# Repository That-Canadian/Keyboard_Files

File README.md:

My Open Source keyboard files will be places here.

-- TODO: Better README --

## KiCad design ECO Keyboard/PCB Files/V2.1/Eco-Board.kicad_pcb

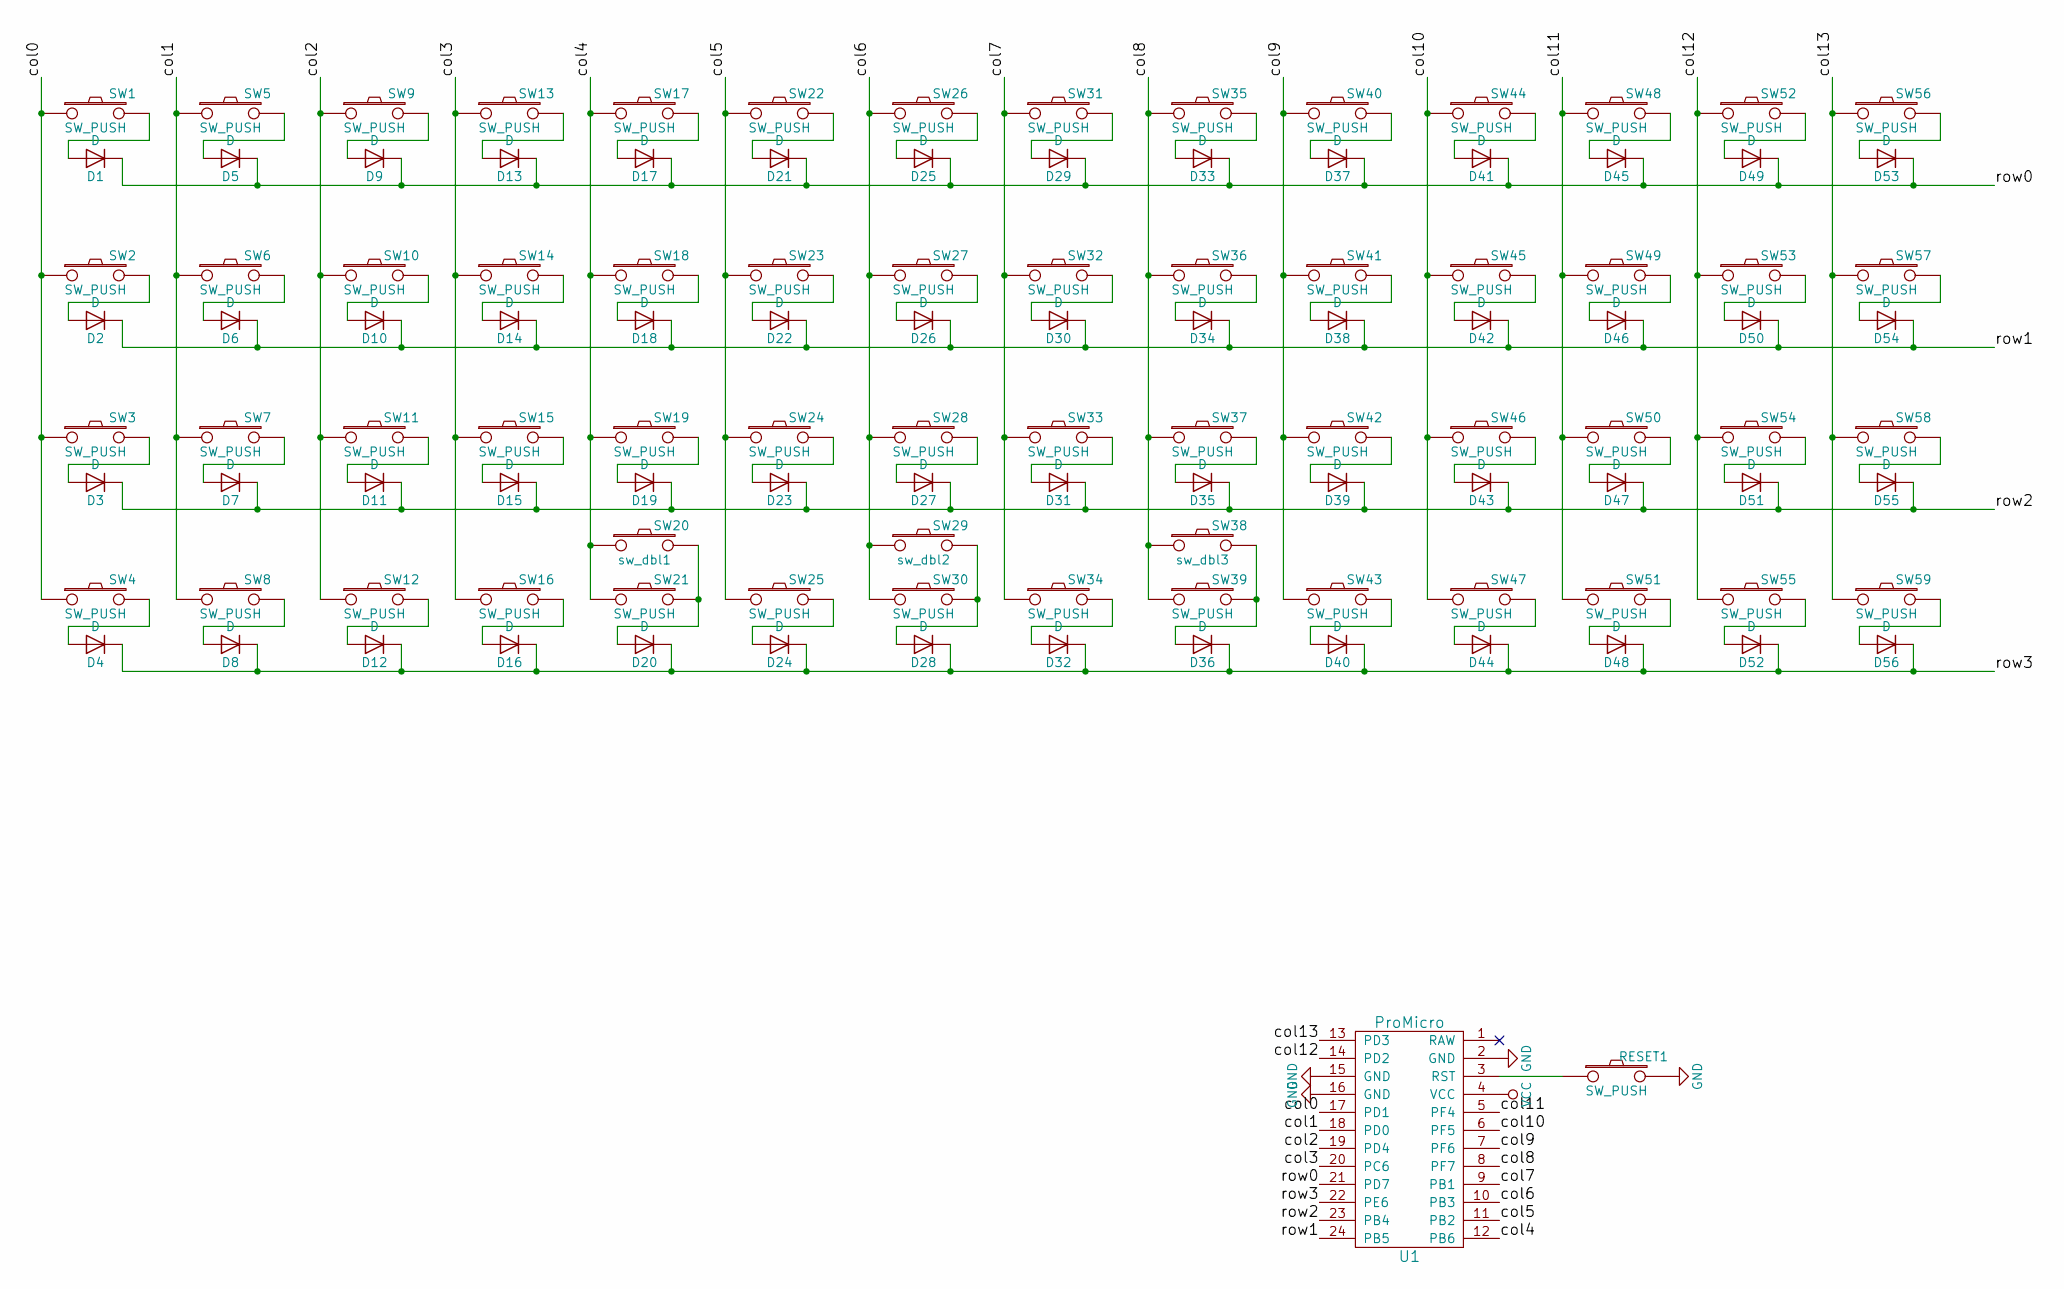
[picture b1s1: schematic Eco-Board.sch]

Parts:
D1, D2, D3, D4, D5, D6, D7, D8, D9, D10, D11, D12, D13, D14, D15, D16, D17, D18, D19, D20, D21, D22, D23, D24, D25, D26, D27, D28, D29, D30, D31, D32, D33, D34, D35, D36, D37, D38, D39, D40, D41, D42, D43, D44, D45, D46, D47, D48, D49, D50, D51, D52, D53, D54, D55, D56: D; D_SOD123_ThroughHole
RESET1: SW_PUSH; SW_TACT_ALPS_SKQGABE010
SW1, SW2, SW3, SW4, SW5, SW6, SW7, SW8, SW9, SW10, SW11, SW12, SW13, SW14, SW15, SW16, SW17, SW18, SW19, SW21, SW22, SW23, SW24, SW25, SW26, SW27, SW28, SW30, SW31, SW32, SW33, SW34, SW35, SW36, SW37, SW39, SW40, SW41, SW42, SW43, SW44, SW45, SW46, SW47, SW48, SW49, SW50, SW51, SW52, SW53, SW54, SW55, SW56, SW57, SW58, SW59: SW_PUSH; Mx_Alps_100
SW20: sw_dbl1; Mx_Alps_200
SW29: sw_dbl2; Mx_Alps_200
SW38: sw_dbl3; Mx_Alps_200
U1: ProMicro; Pro_Micro

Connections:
/col0: SW1.1, SW2.1, SW3.1, SW4.1, U1.17 (PD1)
/col1: SW5.1, SW6.1, SW7.1, SW8.1, U1.18 (PD0)
/col2: SW9.1, SW10.1, SW11.1, SW12.1, U1.19 (PD4)
/col3: SW13.1, SW14.1, SW15.1, SW16.1, U1.20 (PC6)
/col4: SW17.1, SW18.1, SW19.1, SW20.1, SW21.1, U1.12 (PB6)
/col5: SW22.1, SW23.1, SW24.1, SW25.1, U1.11 (PB2)
/col6: SW26.1, SW27.1, SW28.1, SW29.1, SW30.1, U1.10 (PB3)
/col7: SW31.1, SW32.1, SW33.1, SW34.1, U1.9 (PB1)
/col8: SW35.1, SW36.1, SW37.1, SW38.1, SW39.1, U1.8 (PF7)
/col9: SW40.1, SW41.1, SW42.1, SW43.1, U1.7 (PF6)
/col10: SW44.1, SW45.1, SW46.1, SW47.1, U1.6 (PF5)
/col11: SW48.1, SW49.1, SW50.1, SW51.1, U1.5 (PF4)
/col12: SW52.1, SW53.1, SW54.1, SW55.1, U1.14 (PD2)
/col13: SW56.1, SW57.1, SW58.1, SW59.1, U1.13 (PD3)
/row0: D1.1 (K), D5.1 (K), D9.1 (K), D13.1 (K), D17.1 (K), D21.1 (K), D25.1 (K), D29.1 (K), D33.1 (K), D37.1 (K), D41.1 (K), D45.1 (K), D49.1 (K), D53.1 (K), U1.21 (PD7)
/row1: D2.1 (K), D6.1 (K), D10.1 (K), D14.1 (K), D18.1 (K), D22.1 (K), D26.1 (K), D30.1 (K), D34.1 (K), D38.1 (K), D42.1 (K), D46.1 (K), D50.1 (K), D54.1 (K), U1.24 (PB5)
/row2: D3.1 (K), D7.1 (K), D11.1 (K), D15.1 (K), D19.1 (K), D23.1 (K), D27.1 (K), D31.1 (K), D35.1 (K), D39.1 (K), D43.1 (K), D47.1 (K), D51.1 (K), D55.1 (K), U1.23 (PB4)
/row3: D4.1 (K), D8.1 (K), D12.1 (K), D16.1 (K), D20.1 (K), D24.1 (K), D28.1 (K), D32.1 (K), D36.1 (K), D40.1 (K), D44.1 (K), D48.1 (K), D52.1 (K), D56.1 (K), U1.22 (PE6)
GND: RESET1.2, U1.2 (GND), U1.15 (GND), U1.16 (GND)
unnamed: D1.2 (A), SW1.2
unnamed: D2.2 (A), SW2.2
unnamed: D3.2 (A), SW3.2
unnamed: D4.2 (A), SW4.2
unnamed: D5.2 (A), SW5.2
unnamed: D6.2 (A), SW6.2
unnamed: D7.2 (A), SW7.2
unnamed: D8.2 (A), SW8.2
unnamed: D9.2 (A), SW9.2
unnamed: D10.2 (A), SW10.2
unnamed: D11.2 (A), SW11.2
unnamed: D12.2 (A), SW12.2
unnamed: D13.2 (A), SW13.2
unnamed: D14.2 (A), SW14.2
unnamed: D15.2 (A), SW15.2
unnamed: D16.2 (A), SW16.2
unnamed: D17.2 (A), SW17.2
unnamed: D18.2 (A), SW18.2
unnamed: D19.2 (A), SW19.2
unnamed: D20.2 (A), SW20.2, SW21.2
unnamed: D21.2 (A), SW22.2
unnamed: D22.2 (A), SW23.2
unnamed: D23.2 (A), SW24.2
unnamed: D24.2 (A), SW25.2
unnamed: D25.2 (A), SW26.2
unnamed: D26.2 (A), SW27.2
unnamed: D27.2 (A), SW28.2
unnamed: D28.2 (A), SW29.2, SW30.2
unnamed: D29.2 (A), SW31.2
unnamed: D30.2 (A), SW32.2
unnamed: D31.2 (A), SW33.2
unnamed: D32.2 (A), SW34.2
unnamed: D33.2 (A), SW35.2
unnamed: D34.2 (A), SW36.2
unnamed: D35.2 (A), SW37.2
unnamed: D36.2 (A), SW38.2, SW39.2
unnamed: D37.2 (A), SW40.2
unnamed: D38.2 (A), SW41.2
unnamed: D39.2 (A), SW42.2
unnamed: D40.2 (A), SW43.2
unnamed: D41.2 (A), SW44.2
unnamed: D42.2 (A), SW45.2
unnamed: D43.2 (A), SW46.2
unnamed: D44.2 (A), SW47.2
unnamed: D45.2 (A), SW48.2
unnamed: D46.2 (A), SW49.2
unnamed: D47.2 (A), SW50.2
unnamed: D48.2 (A), SW51.2
unnamed: D49.2 (A), SW52.2
unnamed: D50.2 (A), SW53.2
unnamed: D51.2 (A), SW54.2
unnamed: D52.2 (A), SW55.2
unnamed: D53.2 (A), SW56.2
unnamed: D54.2 (A), SW57.2
unnamed: D55.2 (A), SW58.2
unnamed: D56.2 (A), SW59.2
unnamed: RESET1.1, U1.3 (RST)
VCC: U1.4 (VCC)

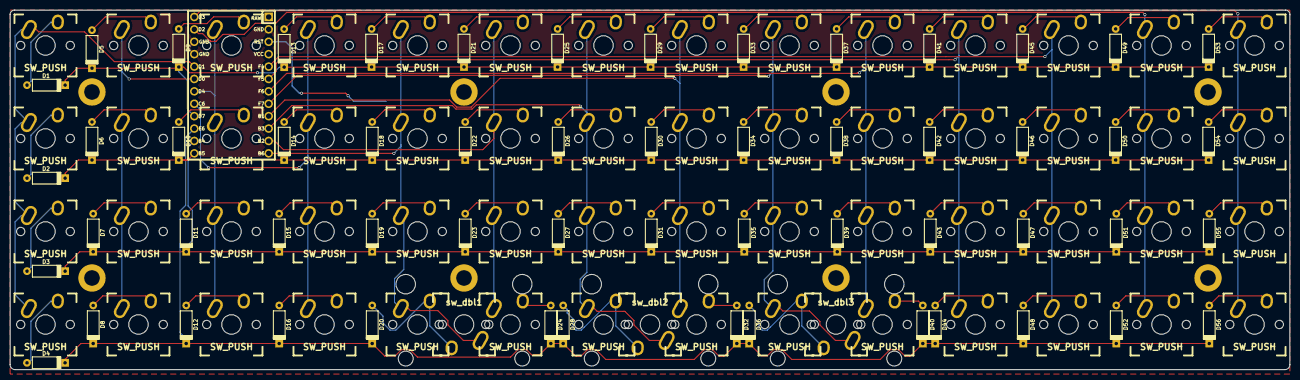
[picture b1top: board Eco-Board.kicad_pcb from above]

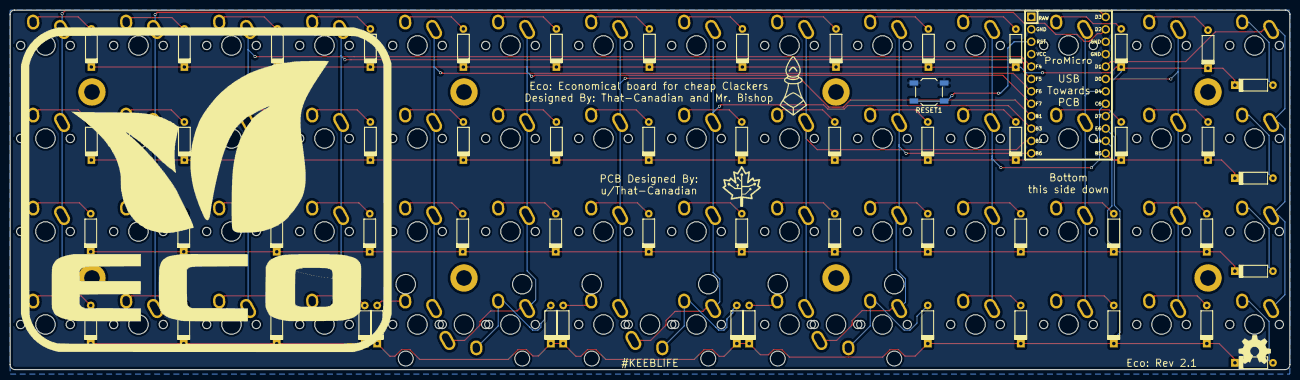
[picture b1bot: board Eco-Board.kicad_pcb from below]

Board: 2 copper layers, 262.1 x 73.6 mm, 117 parts (2 on the bottom side), 76 nets.

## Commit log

2017-09-13 initial commit, readme and ECO case files
2017-11-21 Added ECO PCB files, and KiCAD libs.
